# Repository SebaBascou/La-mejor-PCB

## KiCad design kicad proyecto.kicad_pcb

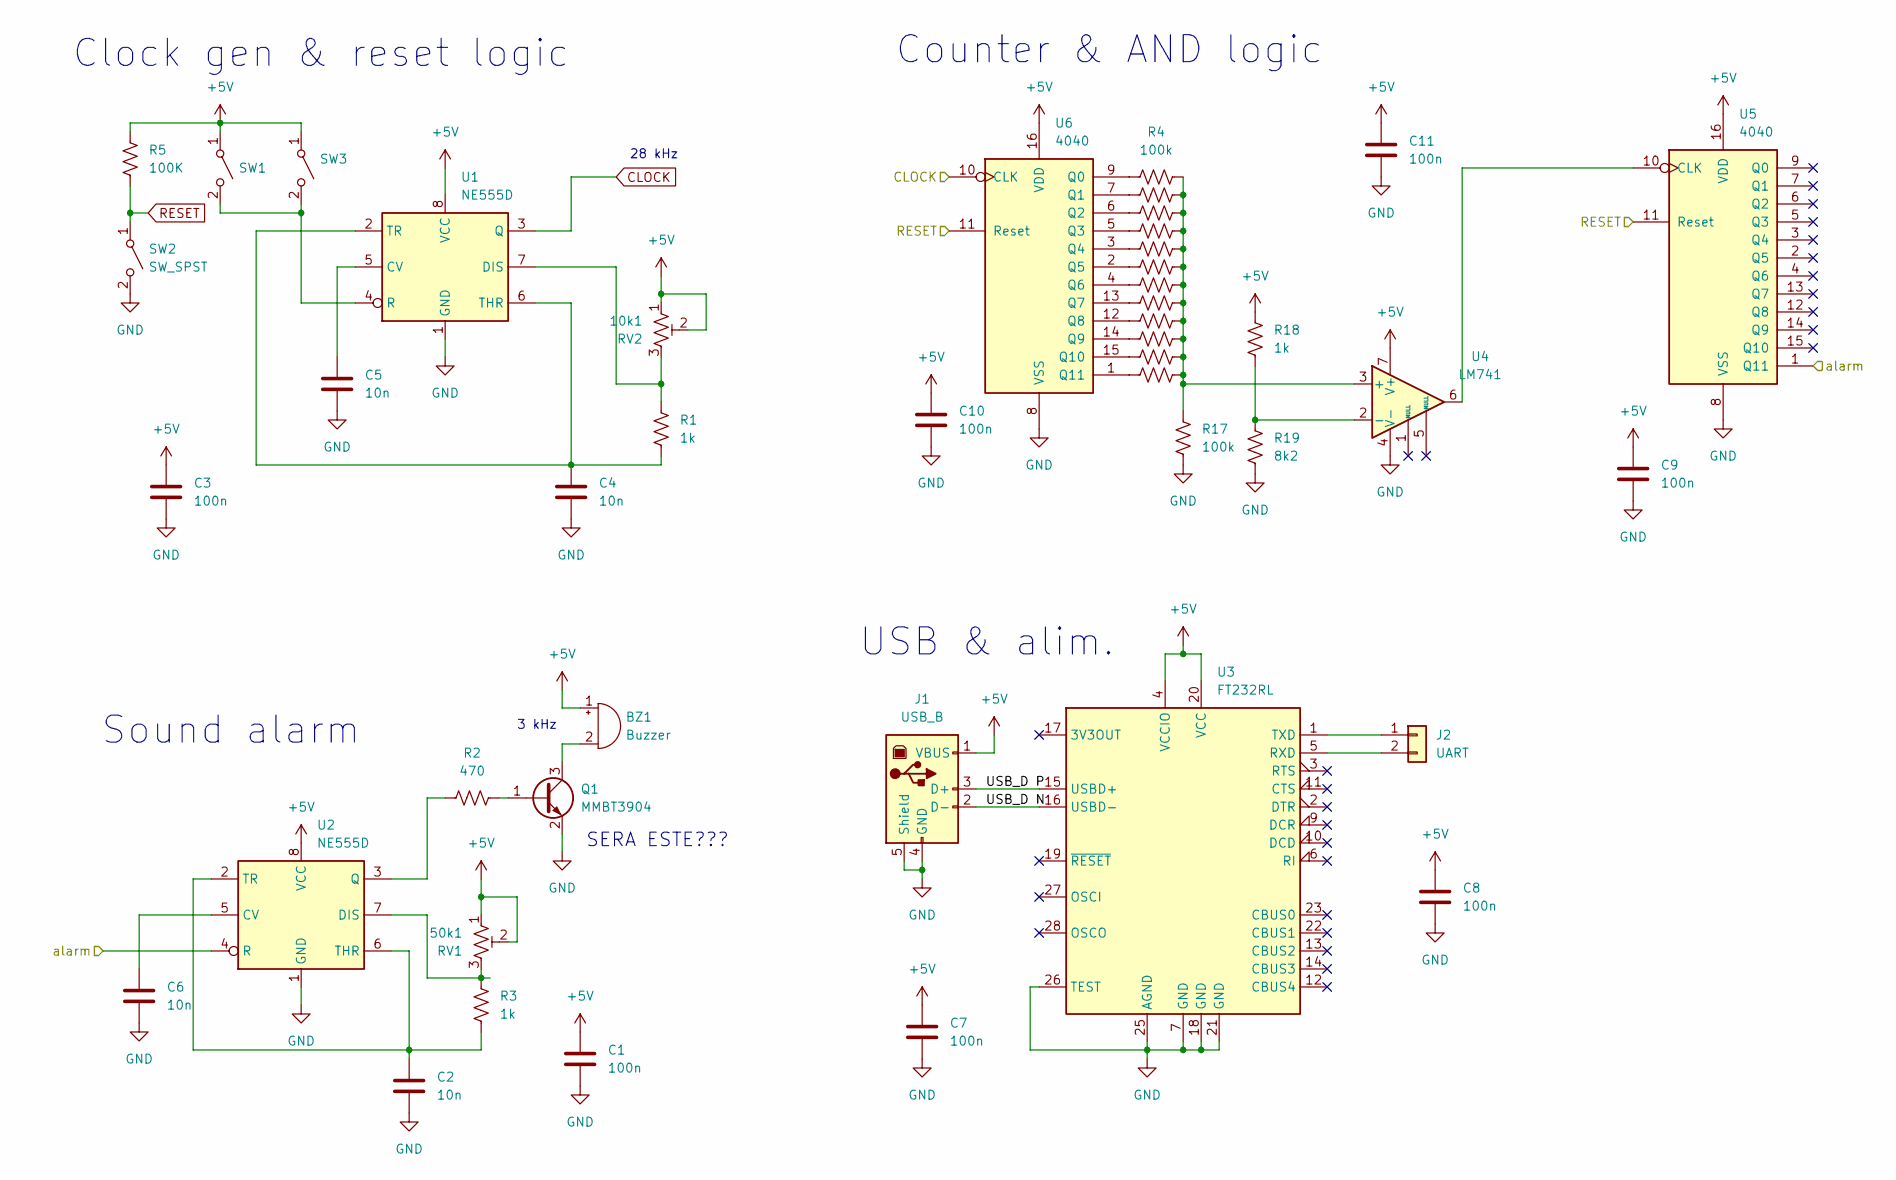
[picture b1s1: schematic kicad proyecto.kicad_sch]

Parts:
10k1: RV2; 601030
50k1: RV1; 601030
BZ1: Buzzer
C1, C3, C7, C8, C9, C10, C11: 100n; C_0603_1608Metric
C2, C4, C5, C6: 10n; C_0603_1608Metric
J1: USB_B; USB_Mini-B_Wuerth_65100516121_Horizontal
J2: UART; PinHeader_1x02_P2.54mm_Vertical
Q1: MMBT3904; SOT-23
R1, R3, R18: 1k; R_0603_1608Metric
R2: 470; R_0603_1608Metric
R4, R6, R7, R8, R9, R10, R11, R12, R13, R14, R15, R16, R17: 100k; R_0603_1608Metric
R5: 100K; R_0603_1608Metric
R19: 8k2; R_0603_1608Metric
SW1, SW2, SW3: SW_SPST; SW_PUSH_6mm_H9.5mm
U1, U2: NE555D; SOIC-8_3.9x4.9mm_P1.27mm
U3: FT232RL; SSOP-28_5.3x10.2mm_P0.65mm
U4: LM741; SOIC-8_3.9x4.9mm_P1.27mm
U5, U6: 4040; SOIC-16_3.9x9.9mm_P1.27mm

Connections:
+5V: 10k1.1, 10k1.2, 50k1.1, 50k1.2, BZ1.1 (+), C1.1, C3.1, C7.1, C8.1, C9.1, C10.1, C11.1, J1.1 (VBUS), R5.1, R18.1, SW1.1 (A), SW3.1 (A), U1.8 (VCC), U2.8 (VCC), U3.4 (VCCIO), U3.20 (VCC), U4.7 (V+), U5.16 (VDD), U6.16 (VDD)
/USB_D N: J1.2 (D-), U3.16 (USBD-)
/USB_D P: J1.3 (D+), U3.15 (USBD+)
/alarm: U2.4 (R), U5.1 (Q11)
CLOCK: U1.3 (Q), U6.10 (CLK)
GND: C1.2, C2.2, C3.2, C4.2, C5.2, C6.2, C7.2, C8.2, C9.2, C10.2, C11.2, J1.4 (GND), J1.5 (Shield), Q1.2 (E), R17.2, R19.2, SW2.2 (B), U1.1 (GND), U2.1 (GND), U3.7 (GND), U3.18 (GND), U3.21 (GND), U3.25 (AGND), U3.26 (TEST), U4.4 (V-), U5.8 (VSS), U6.8 (VSS)
unnamed: BZ1.2 (-), Q1.3 (C)
unnamed: J2.1, U3.1 (TXD)
unnamed: J2.2, U3.5 (RXD)
unnamed: Q1.1 (B), R2.2
unnamed: SW1.2 (B), SW3.2 (B), U1.4 (R)
unnamed: C5.1, U1.5 (CV)
unnamed: 10k1.3, R1.1, U1.7 (DIS)
unnamed: C4.1, R1.2, U1.2 (TR), U1.6 (THR)
unnamed: C6.1, U2.5 (CV)
unnamed: 50k1.3, R3.1, U2.7 (DIS)
unnamed: R2.1, U2.3 (Q)
unnamed: C2.1, R3.2, U2.2 (TR), U2.6 (THR)
unnamed: R4.2, R6.2, R7.2, R8.2, R9.2, R10.2, R11.2, R12.2, R13.2, R14.2, R15.2, R16.2, R17.1, U4.3 (+)
unnamed: R18.2, R19.1, U4.2 (-)
unnamed: U4.6, U5.10 (CLK)
unnamed: R4.1, U6.9 (Q0)
unnamed: R6.1, U6.7 (Q1)
unnamed: R7.1, U6.6 (Q2)
unnamed: R9.1, U6.5 (Q3)
unnamed: R13.1, U6.3 (Q4)
unnamed: R15.1, U6.2 (Q5)
unnamed: R11.1, U6.4 (Q6)
unnamed: R10.1, U6.13 (Q7)
unnamed: R8.1, U6.12 (Q8)
unnamed: R12.1, U6.14 (Q9)
unnamed: R14.1, U6.15 (Q10)
unnamed: R16.1, U6.1 (Q11)
RESET: R5.2, SW2.1 (A), U5.11 (Reset), U6.11 (Reset)

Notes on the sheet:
28 kHz
Clock gen & reset logic
Sound alarm
3 kHz
Counter & AND logic
SERA ESTE???
USB & alim.

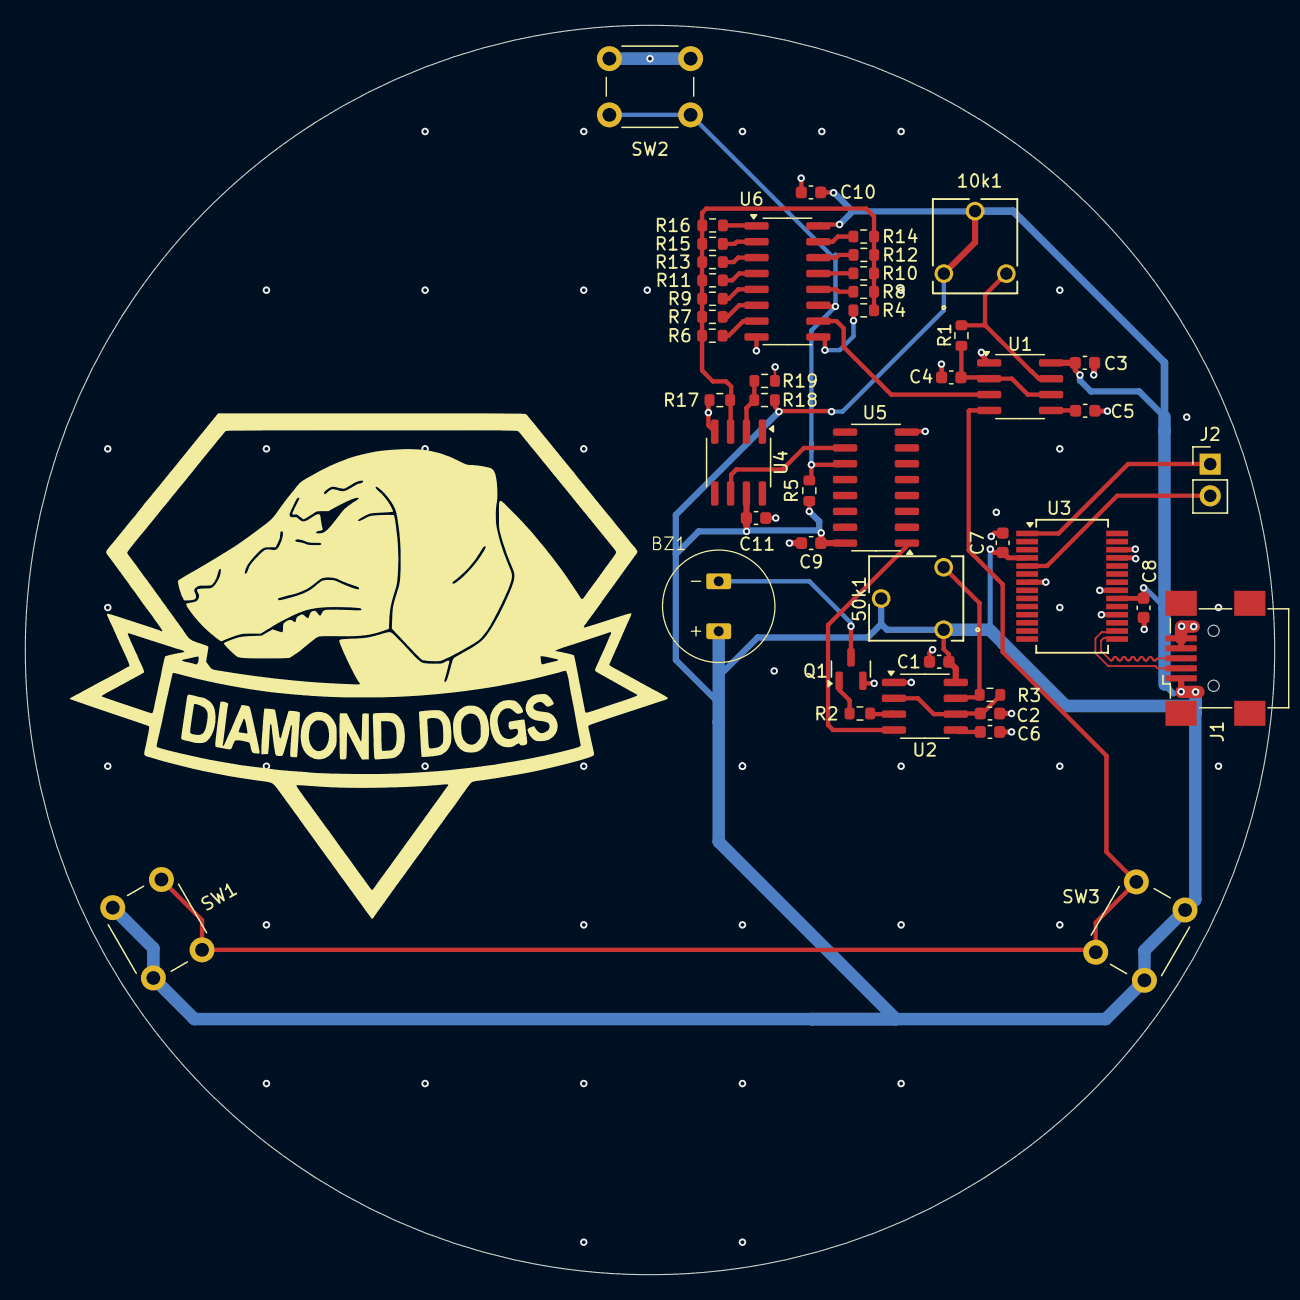
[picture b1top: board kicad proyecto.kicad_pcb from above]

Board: 4 copper layers, 100.0 x 100.0 mm, 45 parts (0 on the bottom side), 34 nets.

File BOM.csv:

"","Sourced","Placed","References","Value","Footprint","Quantity"
1,"","","C1, C3, C7, C8, C9, C10, C11","100n","C_0603_1608Metric",7
2,"","","C2, C4, C5, C6","10n","C_0603_1608Metric",4
3,"","","R4, R5, R6, R7, R8, R9, R10, R11, R12, R13, R14, R15, R16, R17","100k","R_0603_1608Metric",14
4,"","","R1, R3, R18","1k","R_0603_1608Metric",3
5,"","","R2",470,"R_0603_1608Metric",1
6,"","","R19","8k2","R_0603_1608Metric",1
7,"","","U1, U2","NE555D","SOIC-8_3.9x4.9mm_P1.27mm",2
8,"","","U5, U6",4040,"SOIC-16_3.9x9.9mm_P1.27mm",2
9,"","","U3","FT232RL","SSOP-28_5.3x10.2mm_P0.65mm",1
10,"","","U4","LM741","SOIC-8_3.9x4.9mm_P1.27mm",1
11,"","","SW1, SW2, SW3","SW_SPST","SW_PUSH_6mm_H9.5mm",3
12,"","","10k1","RV2","Potentiometer_ACP_CA6-H2,5_Horizontal",1
13,"","","50k1","RV1","Potentiometer_ACP_CA6-H2,5_Horizontal",1
14,"","","BZ1","Buzzer","Buzzer",1
15,"","","Q1","MMBT3904","SOT-23",1
16,"","","J1","USB_B","USB_Mini-B_Wuerth_65100516121_Horizontal",1
17,"","","J2","UART","PinHeader_1x02_P2.54mm_Vertical",1

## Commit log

2025-05-03 Crear BOM desde la extension en html
2025-05-03 ancho de las bandas a 0.35mm
2025-05-03 Ruteo completo para baja frecuencia
2025-05-08 REMapeo
2025-05-12 routeo de una pista al plano superior en vez de vias
    movi una pista al plano superior y modifique el ancho de algunas pistas de power, agregue stitching al resto de la placa
2025-05-12 BOM actualizado en el csv
2025-05-12 geber
2025-05-12 Corregir gerber
2025-05-12 zip de gerber
